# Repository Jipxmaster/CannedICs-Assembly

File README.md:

Son archivos viejos que tengo
-El compilador es un ejecutable que usa el archivo config
-EL archivo de la computadora está en formato .circ para logisim
-Correr la simulación a 4096 Hz, es muy lento

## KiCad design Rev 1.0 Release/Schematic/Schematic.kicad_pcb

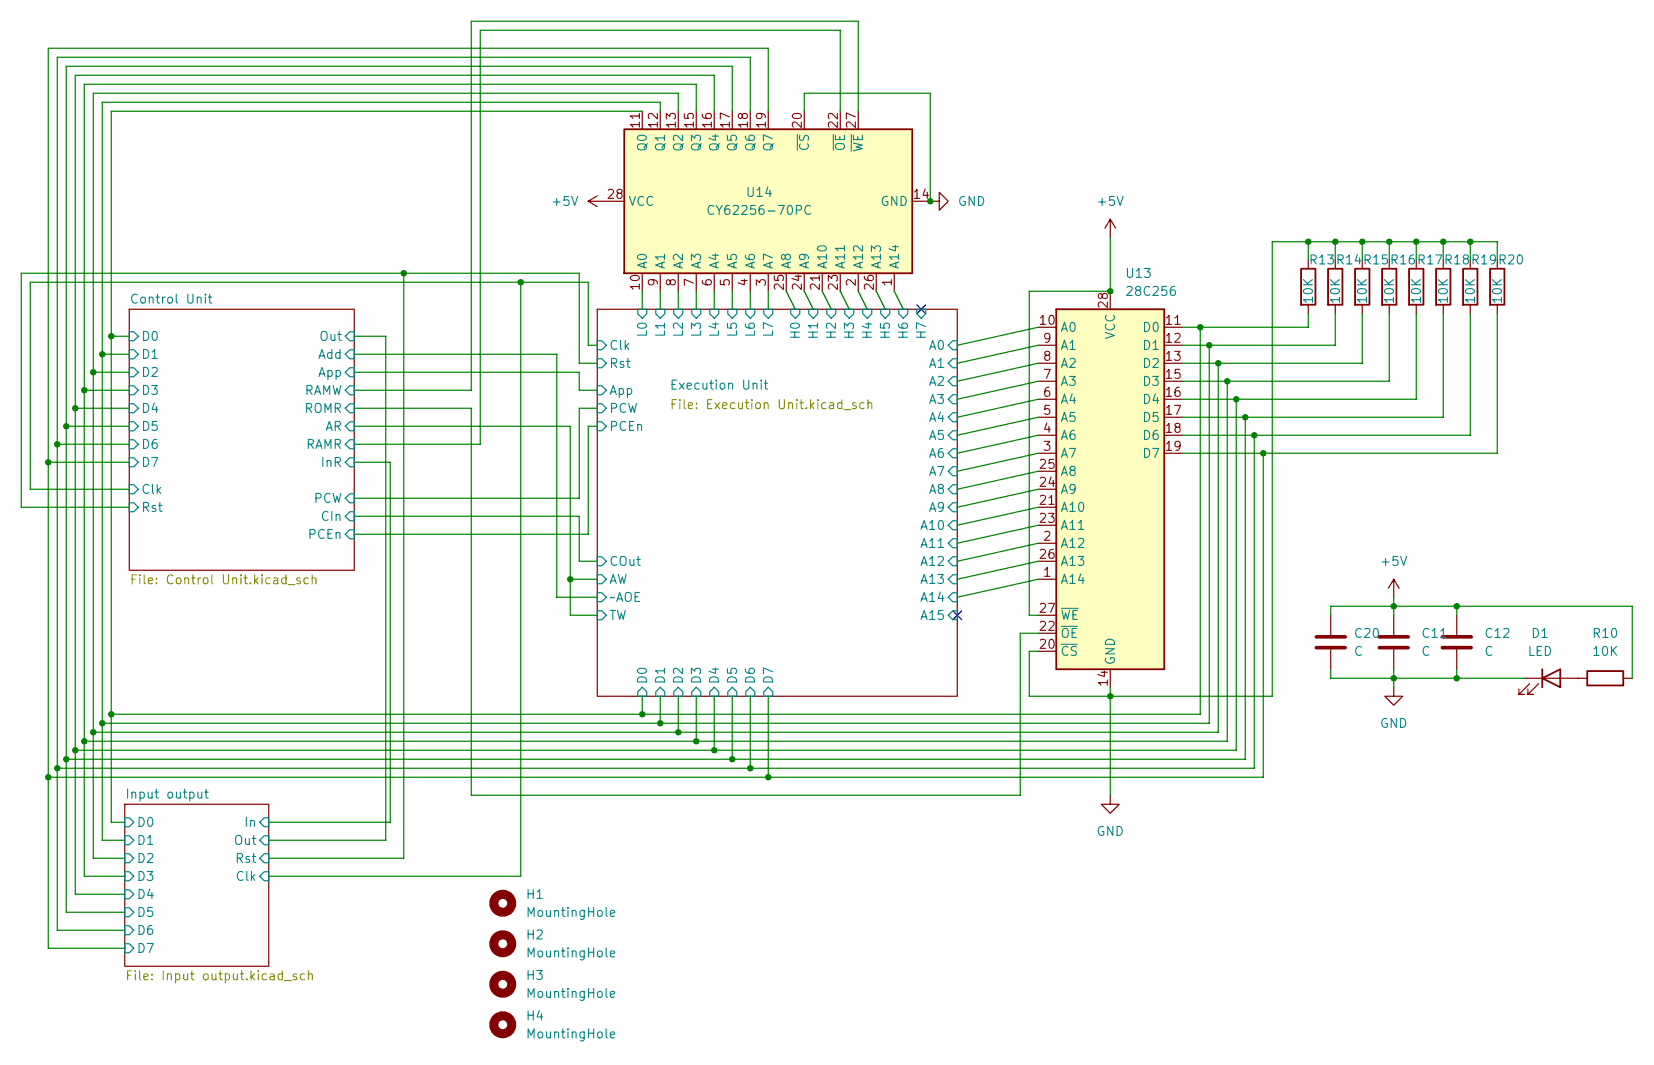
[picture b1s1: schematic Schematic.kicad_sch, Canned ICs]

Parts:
C11, C12: C; C_Disc_D3.8mm_W2.6mm_P2.50mm
C20: C; C_Radial_D5.0mm_H11.0mm_P2.00mm
D1: LED; LED_D3.0mm_Clear
H1, H2, H3, H4: MountingHole; MountingHole_3.2mm_M3_ISO7380
R10: 10K; R_Axial_DIN0204_L3.6mm_D1.6mm_P7.62mm_Horizontal
R13, R14, R15, R16, R17, R18, R19, R20: 10K; R_Axial_DIN0204_L3.6mm_D1.6mm_P2.54mm_Vertical
U13: 28C256; DIP-28_W15.24mm
U14: CY62256-70PC; DIP-28_W15.24mm

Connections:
+5V: C11.1, C12.1, C20.1, R10.2, U13.27 (~WE), U13.28 (VCC), U14.28 (VCC); also elsewhere on the board
/Control Unit/D0: R13.2, U13.11 (D0), U14.11 (Q0); also elsewhere on the board
/Control Unit/D1: R14.2, U13.12 (D1), U14.12 (Q1); also elsewhere on the board
/Control Unit/D2: R15.2, U13.13 (D2), U14.13 (Q2); also elsewhere on the board
/Control Unit/D3: R16.2, U13.15 (D3), U14.15 (Q3); also elsewhere on the board
/Control Unit/D4: R17.2, U13.16 (D4), U14.16 (Q4); also elsewhere on the board
/Control Unit/D5: R18.2, U13.17 (D5), U14.17 (Q5); also elsewhere on the board
/Control Unit/D6: R19.2, U13.18 (D6), U14.18 (Q6); also elsewhere on the board
/Control Unit/D7: R20.2, U13.19 (D7), U14.19 (Q7); also elsewhere on the board
/Control Unit/RAMR: U14.22 (~OE); also elsewhere on the board
/Control Unit/RAMW: U14.27 (~WE); also elsewhere on the board
/Control Unit/ROMR: U13.22 (~OE); also elsewhere on the board
/Execution Unit/A0: U13.10 (A0); also elsewhere on the board
/Execution Unit/A1: U13.9 (A1); also elsewhere on the board
/Execution Unit/A2: U13.8 (A2); also elsewhere on the board
/Execution Unit/A3: U13.7 (A3); also elsewhere on the board
/Execution Unit/A4: U13.6 (A4); also elsewhere on the board
/Execution Unit/A5: U13.5 (A5); also elsewhere on the board
/Execution Unit/A6: U13.4 (A6); also elsewhere on the board
/Execution Unit/A7: U13.3 (A7); also elsewhere on the board
/Execution Unit/A8: U13.25 (A8); also elsewhere on the board
/Execution Unit/A9: U13.24 (A9); also elsewhere on the board
/Execution Unit/A10: U13.21 (A10); also elsewhere on the board
/Execution Unit/A11: U13.23 (A11); also elsewhere on the board
/Execution Unit/A12: U13.2 (A12); also elsewhere on the board
/Execution Unit/A13: U13.26 (A13); also elsewhere on the board
/Execution Unit/A14: U13.1 (A14); also elsewhere on the board
/Execution Unit/H0: U14.25 (A8); also elsewhere on the board
/Execution Unit/H1: U14.24 (A9); also elsewhere on the board
/Execution Unit/H2: U14.21 (A10); also elsewhere on the board
/Execution Unit/H3: U14.23 (A11); also elsewhere on the board
/Execution Unit/H4: U14.2 (A12); also elsewhere on the board
/Execution Unit/H5: U14.26 (A13); also elsewhere on the board
/Execution Unit/H6: U14.1 (A14); also elsewhere on the board
/Execution Unit/L0: U14.10 (A0); also elsewhere on the board
/Execution Unit/L1: U14.9 (A1); also elsewhere on the board
/Execution Unit/L2: U14.8 (A2); also elsewhere on the board
/Execution Unit/L3: U14.7 (A3); also elsewhere on the board
/Execution Unit/L4: U14.6 (A4); also elsewhere on the board
/Execution Unit/L5: U14.5 (A5); also elsewhere on the board
/Execution Unit/L6: U14.4 (A6); also elsewhere on the board
/Execution Unit/L7: U14.3 (A7); also elsewhere on the board
GND: C11.2, C12.2, C20.2, D1.1 (K), R13.1, R14.1, R15.1, R16.1, R17.1, R18.1, R19.1, R20.1, U13.14 (GND), U13.20 (~CS), U14.14 (GND), U14.20 (~CS); also elsewhere on the board
unnamed: D1.2 (A), R10.1

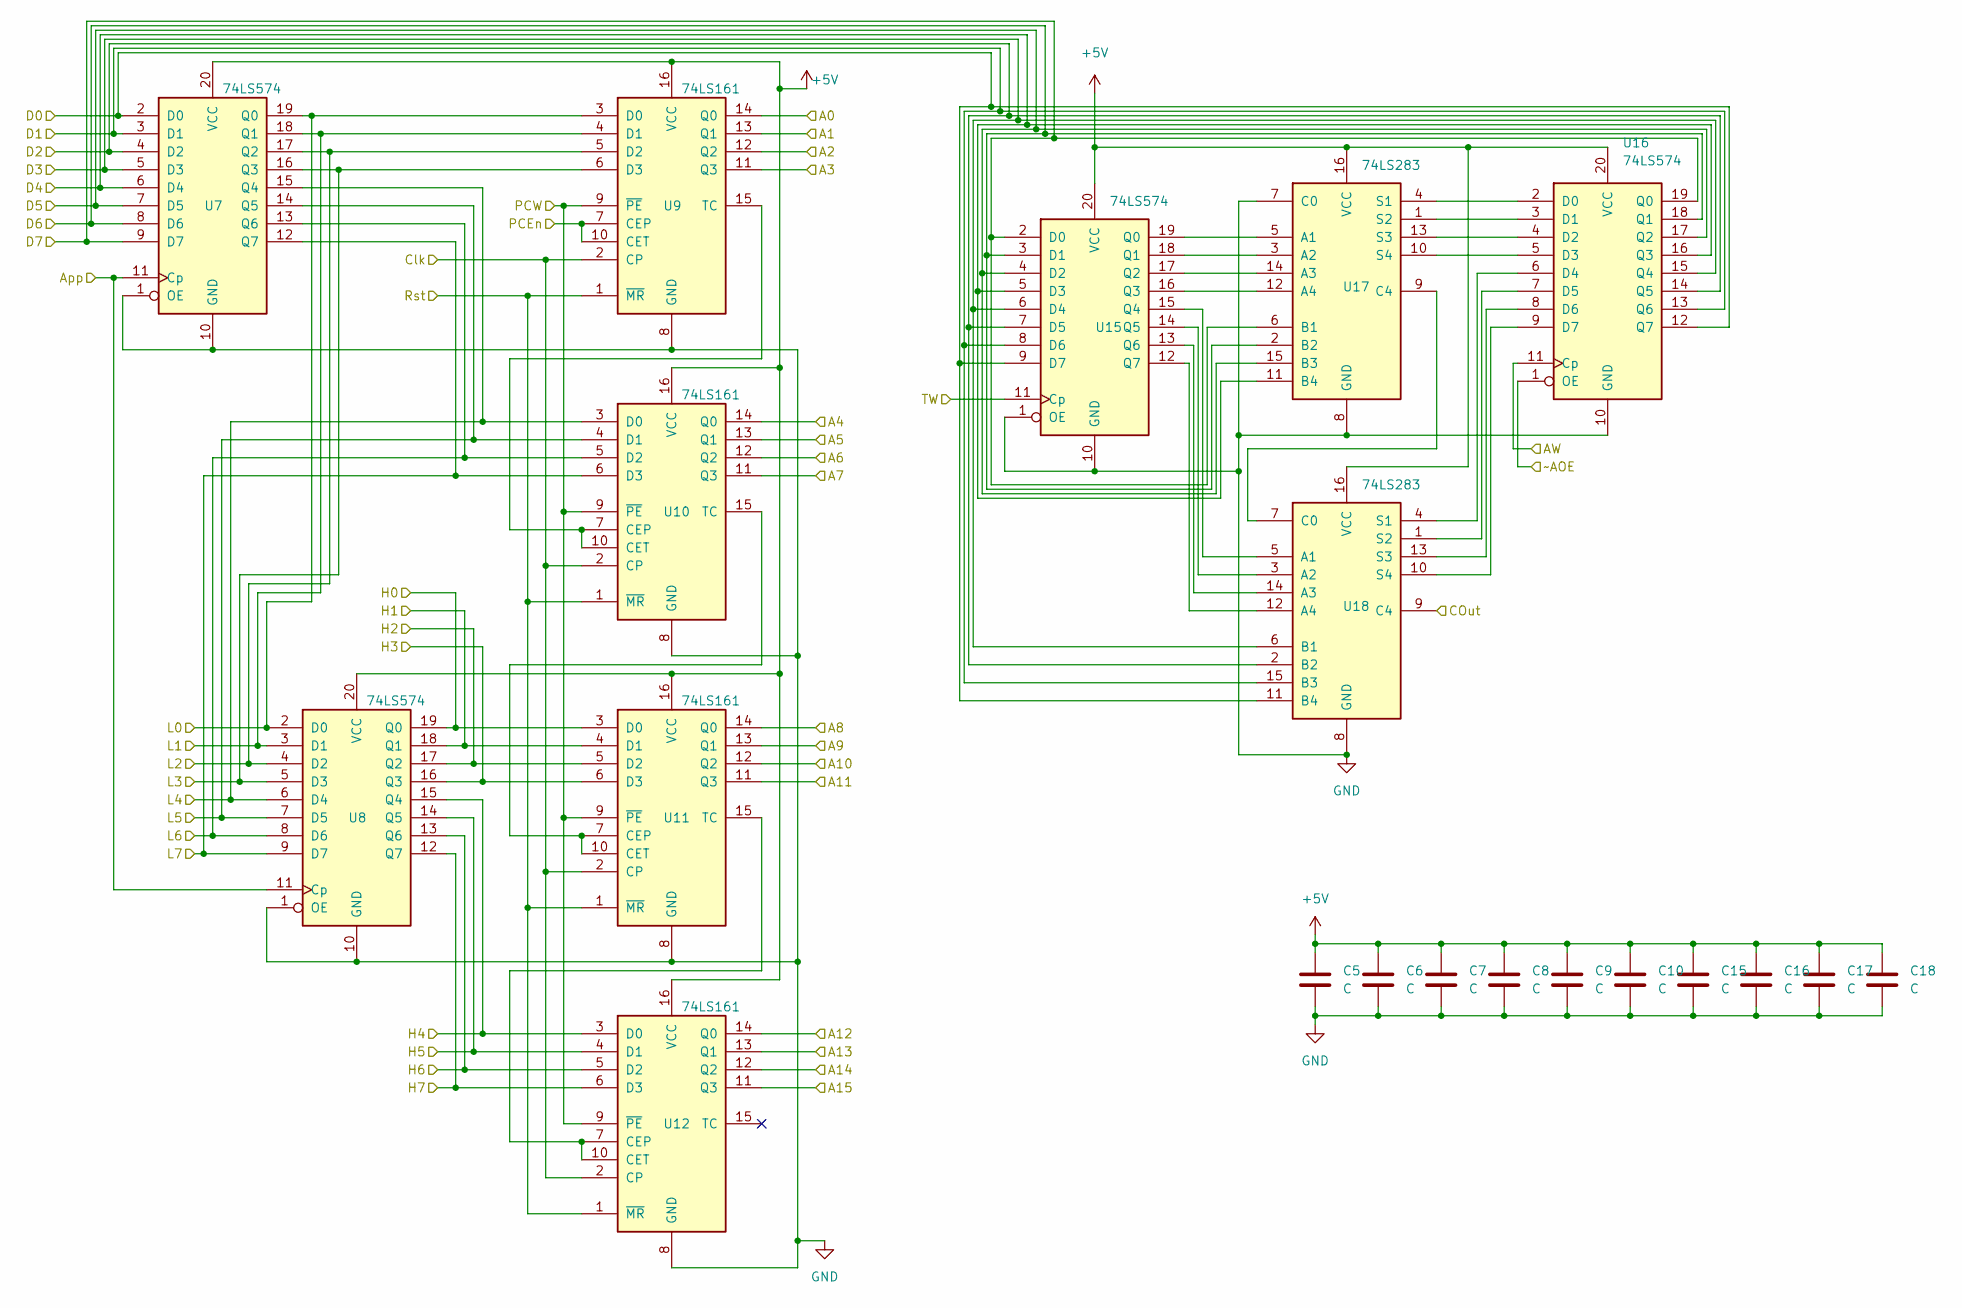
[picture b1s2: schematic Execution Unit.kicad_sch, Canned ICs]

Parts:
C5, C6, C7, C8, C9, C10, C15, C16, C17, C18: C; C_Disc_D3.8mm_W2.6mm_P2.50mm
U7, U8, U15, U16: 74LS574; DIP-20_W7.62mm
U9, U10, U11, U12: 74LS161; DIP-16_W7.62mm
U17, U18: 74LS283; DIP-16_W7.62mm

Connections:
+5V: C5.1, C6.1, C7.1, C8.1, C9.1, C10.1, C15.1, C16.1, C17.1, C18.1, U7.20 (VCC), U8.20 (VCC), U9.16 (VCC), U10.16 (VCC), U11.16 (VCC), U12.16 (VCC), U15.20 (VCC), U16.20 (VCC), U17.16 (VCC), U18.16 (VCC); also elsewhere on the board
/Control Unit/AR: U15.11 (Cp), U16.11 (Cp); also elsewhere on the board
/Control Unit/Add: U16.1 (OE); also elsewhere on the board
/Control Unit/App: U7.11 (Cp), U8.11 (Cp); also elsewhere on the board
/Control Unit/CIn: U18.9 (C4); also elsewhere on the board
/Control Unit/Clk: U9.2 (CP), U10.2 (CP), U11.2 (CP), U12.2 (CP); also elsewhere on the board
/Control Unit/D0: U7.2 (D0), U15.9 (D7), U16.12 (Q7), U18.11 (B4); also elsewhere on the board
/Control Unit/D1: U7.3 (D1), U15.8 (D6), U16.13 (Q6), U18.15 (B3); also elsewhere on the board
/Control Unit/D2: U7.4 (D2), U15.7 (D5), U16.14 (Q5), U18.2 (B2); also elsewhere on the board
/Control Unit/D3: U7.5 (D3), U15.6 (D4), U16.15 (Q4), U18.6 (B1); also elsewhere on the board
/Control Unit/D4: U7.6 (D4), U15.5 (D3), U16.16 (Q3), U17.11 (B4); also elsewhere on the board
/Control Unit/D5: U7.7 (D5), U15.4 (D2), U16.17 (Q2), U17.15 (B3); also elsewhere on the board
/Control Unit/D6: U7.8 (D6), U15.3 (D1), U16.18 (Q1), U17.2 (B2); also elsewhere on the board
/Control Unit/D7: U7.9 (D7), U15.2 (D0), U16.19 (Q0), U17.6 (B1); also elsewhere on the board
/Control Unit/PCEn: U9.7 (CEP), U9.10 (CET); also elsewhere on the board
/Control Unit/PCW: U9.9 (~PE), U10.9 (~PE), U11.9 (~PE), U12.9 (~PE); also elsewhere on the board
/Control Unit/Rst: U9.1 (~MR), U10.1 (~MR), U11.1 (~MR), U12.1 (~MR); also elsewhere on the board
/Execution Unit/A0: U9.14 (Q0); also elsewhere on the board
/Execution Unit/A1: U9.13 (Q1); also elsewhere on the board
/Execution Unit/A2: U9.12 (Q2); also elsewhere on the board
/Execution Unit/A3: U9.11 (Q3); also elsewhere on the board
/Execution Unit/A4: U10.14 (Q0); also elsewhere on the board
/Execution Unit/A5: U10.13 (Q1); also elsewhere on the board
/Execution Unit/A6: U10.12 (Q2); also elsewhere on the board
/Execution Unit/A7: U10.11 (Q3); also elsewhere on the board
/Execution Unit/A8: U11.14 (Q0); also elsewhere on the board
/Execution Unit/A9: U11.13 (Q1); also elsewhere on the board
/Execution Unit/A10: U11.12 (Q2); also elsewhere on the board
/Execution Unit/A11: U11.11 (Q3); also elsewhere on the board
/Execution Unit/A12: U12.14 (Q0); also elsewhere on the board
/Execution Unit/A13: U12.13 (Q1); also elsewhere on the board
/Execution Unit/A14: U12.12 (Q2); also elsewhere on the board
/Execution Unit/A15: U12.11 (Q3)
/Execution Unit/H0: U8.19 (Q0), U11.3 (D0); also elsewhere on the board
/Execution Unit/H1: U8.18 (Q1), U11.4 (D1); also elsewhere on the board
/Execution Unit/H2: U8.17 (Q2), U11.5 (D2); also elsewhere on the board
/Execution Unit/H3: U8.16 (Q3), U11.6 (D3); also elsewhere on the board
/Execution Unit/H4: U8.15 (Q4), U12.3 (D0); also elsewhere on the board
/Execution Unit/H5: U8.14 (Q5), U12.4 (D1); also elsewhere on the board
/Execution Unit/H6: U8.13 (Q6), U12.5 (D2); also elsewhere on the board
/Execution Unit/H7: U8.12 (Q7), U12.6 (D3)
/Execution Unit/L0: U7.19 (Q0), U8.2 (D0), U9.3 (D0); also elsewhere on the board
/Execution Unit/L1: U7.18 (Q1), U8.3 (D1), U9.4 (D1); also elsewhere on the board
/Execution Unit/L2: U7.17 (Q2), U8.4 (D2), U9.5 (D2); also elsewhere on the board
/Execution Unit/L3: U7.16 (Q3), U8.5 (D3), U9.6 (D3); also elsewhere on the board
/Execution Unit/L4: U7.15 (Q4), U8.6 (D4), U10.3 (D0); also elsewhere on the board
/Execution Unit/L5: U7.14 (Q5), U8.7 (D5), U10.4 (D1); also elsewhere on the board
/Execution Unit/L6: U7.13 (Q6), U8.8 (D6), U10.5 (D2); also elsewhere on the board
/Execution Unit/L7: U7.12 (Q7), U8.9 (D7), U10.6 (D3); also elsewhere on the board
GND: C5.2, C6.2, C7.2, C8.2, C9.2, C10.2, C15.2, C16.2, C17.2, C18.2, U7.1 (OE), U7.10 (GND), U8.1 (OE), U8.10 (GND), U9.8 (GND), U10.8 (GND), U11.8 (GND), U12.8 (GND), U15.1 (OE), U15.10 (GND), U16.10 (GND), U17.7 (C0), U17.8 (GND), U18.8 (GND); also elsewhere on the board
unnamed: U9.15 (TC), U10.7 (CEP), U10.10 (CET)
unnamed: U10.15 (TC), U11.7 (CEP), U11.10 (CET)
unnamed: U11.15 (TC), U12.7 (CEP), U12.10 (CET)
unnamed: U15.12 (Q7), U18.12 (A4)
unnamed: U15.13 (Q6), U18.14 (A3)
unnamed: U15.14 (Q5), U18.3 (A2)
unnamed: U15.15 (Q4), U18.5 (A1)
unnamed: U15.16 (Q3), U17.12 (A4)
unnamed: U15.17 (Q2), U17.14 (A3)
unnamed: U15.18 (Q1), U17.3 (A2)
unnamed: U15.19 (Q0), U17.5 (A1)
unnamed: U16.2 (D0), U17.4 (S1)
unnamed: U16.3 (D1), U17.1 (S2)
unnamed: U16.4 (D2), U17.13 (S3)
unnamed: U16.5 (D3), U17.10 (S4)
unnamed: U16.6 (D4), U18.4 (S1)
unnamed: U16.7 (D5), U18.1 (S2)
unnamed: U16.8 (D6), U18.13 (S3)
unnamed: U16.9 (D7), U18.10 (S4)
unnamed: U17.9 (C4), U18.7 (C0)

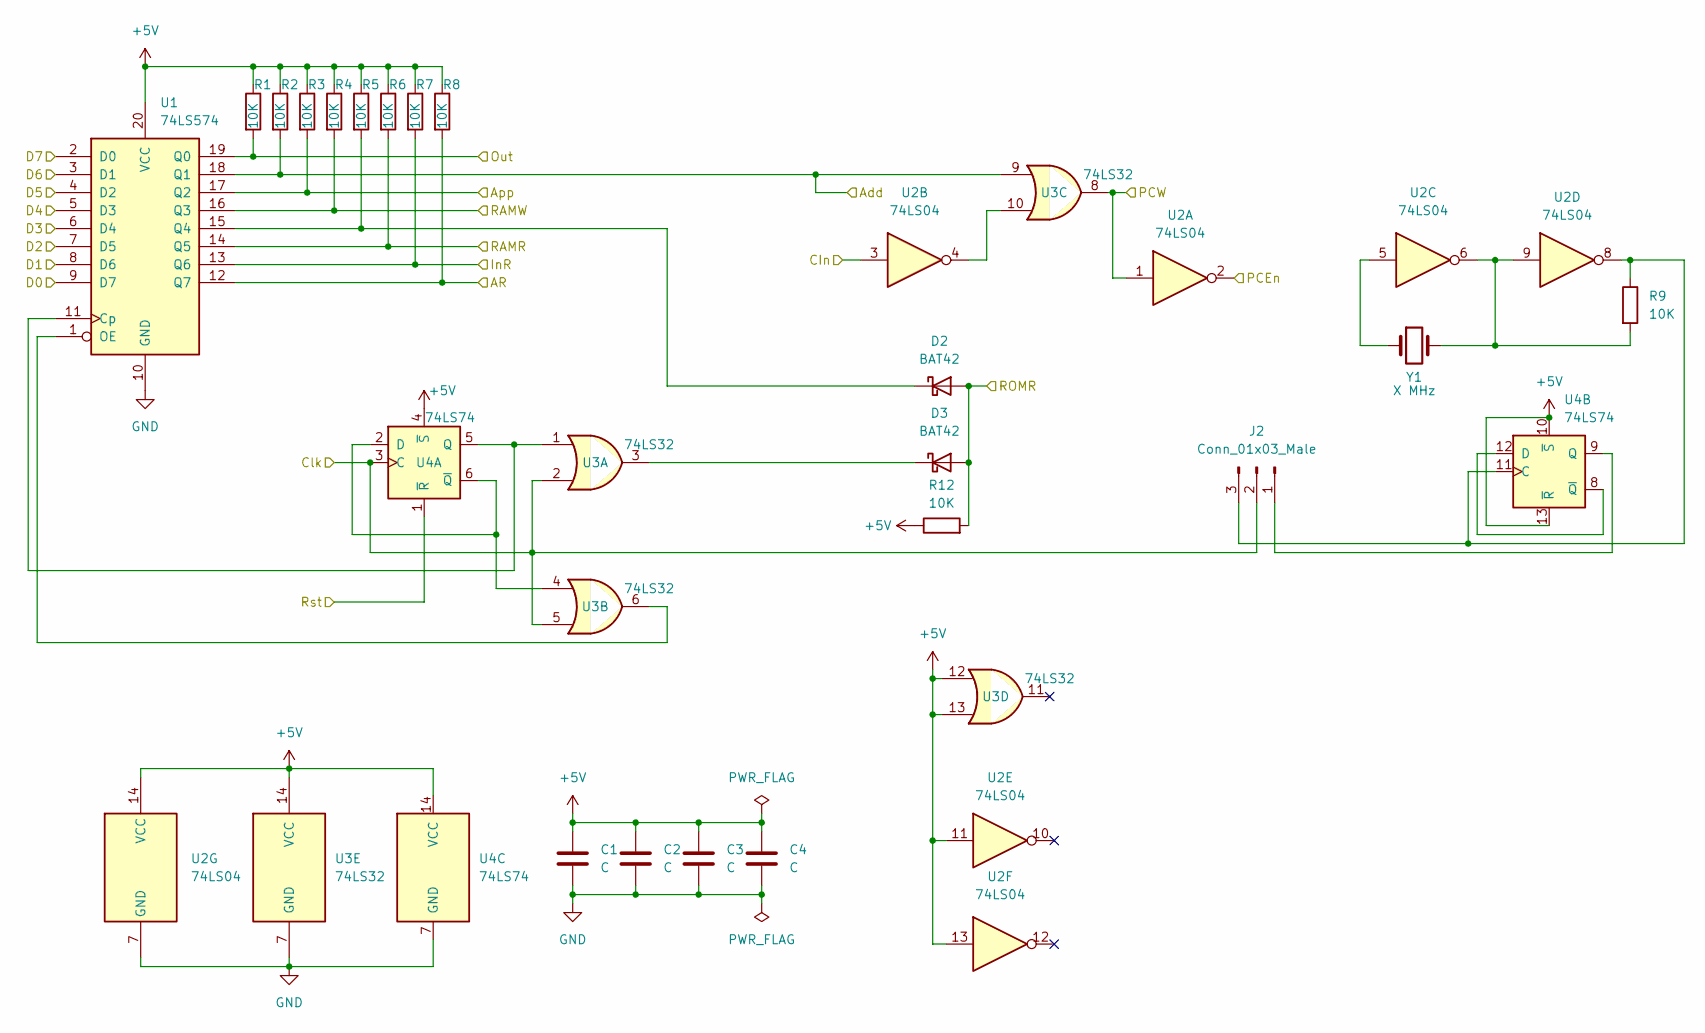
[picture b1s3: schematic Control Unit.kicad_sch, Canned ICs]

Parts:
C1, C2, C3, C4: C; C_Disc_D3.8mm_W2.6mm_P2.50mm
D2, D3: BAT42; D_DO-35_SOD27_P2.54mm_Vertical_AnodeUp
J2: Conn_01x03_Male; PinHeader_1x03_P2.54mm_Vertical
R1, R2, R3, R4, R5, R6, R7, R8, R9, R12: 10K; R_Axial_DIN0204_L3.6mm_D1.6mm_P2.54mm_Vertical
U1: 74LS574; DIP-20_W7.62mm
U2: 74LS04; DIP-14_W7.62mm
U3: 74LS32; DIP-14_W7.62mm
U4: 74LS74; DIP-14_W7.62mm
Y1: X MHz; Crystal_HC18-U_Vertical

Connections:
+5V: C1.1, C2.1, C3.1, C4.1, R1.1, R2.1, R3.1, R4.1, R5.1, R6.1, R7.1, R8.1, R12.1, U1.20 (VCC), U2.11, U2.13, U2.14 (VCC), U3.12, U3.13, U3.14 (VCC), U4.4 (~S), U4.10 (~S), U4.13 (~R), U4.14 (VCC); also elsewhere on the board
/Control Unit/AR: R8.2, U1.12 (Q7); also elsewhere on the board
/Control Unit/Add: R2.2, U1.18 (Q1), U3.9; also elsewhere on the board
/Control Unit/App: R3.2, U1.17 (Q2); also elsewhere on the board
/Control Unit/CIn: U2.3; also elsewhere on the board
/Control Unit/Clk: J2.2, U3.2, U3.5, U4.3 (C); also elsewhere on the board
/Control Unit/D0: U1.9 (D7); also elsewhere on the board
/Control Unit/D1: U1.8 (D6); also elsewhere on the board
/Control Unit/D2: U1.7 (D5); also elsewhere on the board
/Control Unit/D3: U1.6 (D4); also elsewhere on the board
/Control Unit/D4: U1.5 (D3); also elsewhere on the board
/Control Unit/D5: U1.4 (D2); also elsewhere on the board
/Control Unit/D6: U1.3 (D1); also elsewhere on the board
/Control Unit/D7: U1.2 (D0); also elsewhere on the board
/Control Unit/InR: R7.2, U1.13 (Q6); also elsewhere on the board
/Control Unit/Out: R1.2, U1.19 (Q0); also elsewhere on the board
/Control Unit/PCEn: U2.2; also elsewhere on the board
/Control Unit/PCW: U2.1, U3.8; also elsewhere on the board
/Control Unit/RAMR: R6.2, U1.14 (Q5); also elsewhere on the board
/Control Unit/RAMW: R4.2, U1.16 (Q3); also elsewhere on the board
/Control Unit/ROMR: D2.2 (A), D3.2 (A), R12.2; also elsewhere on the board
/Control Unit/Rst: U4.1 (~R); also elsewhere on the board
GND: C1.2, C2.2, C3.2, C4.2, U1.10 (GND), U2.7 (GND), U3.7 (GND), U4.7 (GND); also elsewhere on the board
unnamed: D2.1 (K), R5.2, U1.15 (Q4)
unnamed: D3.1 (K), U3.3
unnamed: J2.3, R9.1, U2.8, U4.11 (C)
unnamed: R9.2, U2.6, U2.9, Y1.2
unnamed: U1.1 (OE), U3.6
unnamed: U1.11 (Cp), U3.1, U4.5 (Q)
unnamed: U2.4, U3.10
unnamed: U2.5, Y1.1
unnamed: U3.4, U4.2 (D), U4.6 (~Q)
unnamed: J2.1, U4.9 (Q)
unnamed: U4.8 (~Q), U4.12 (D)

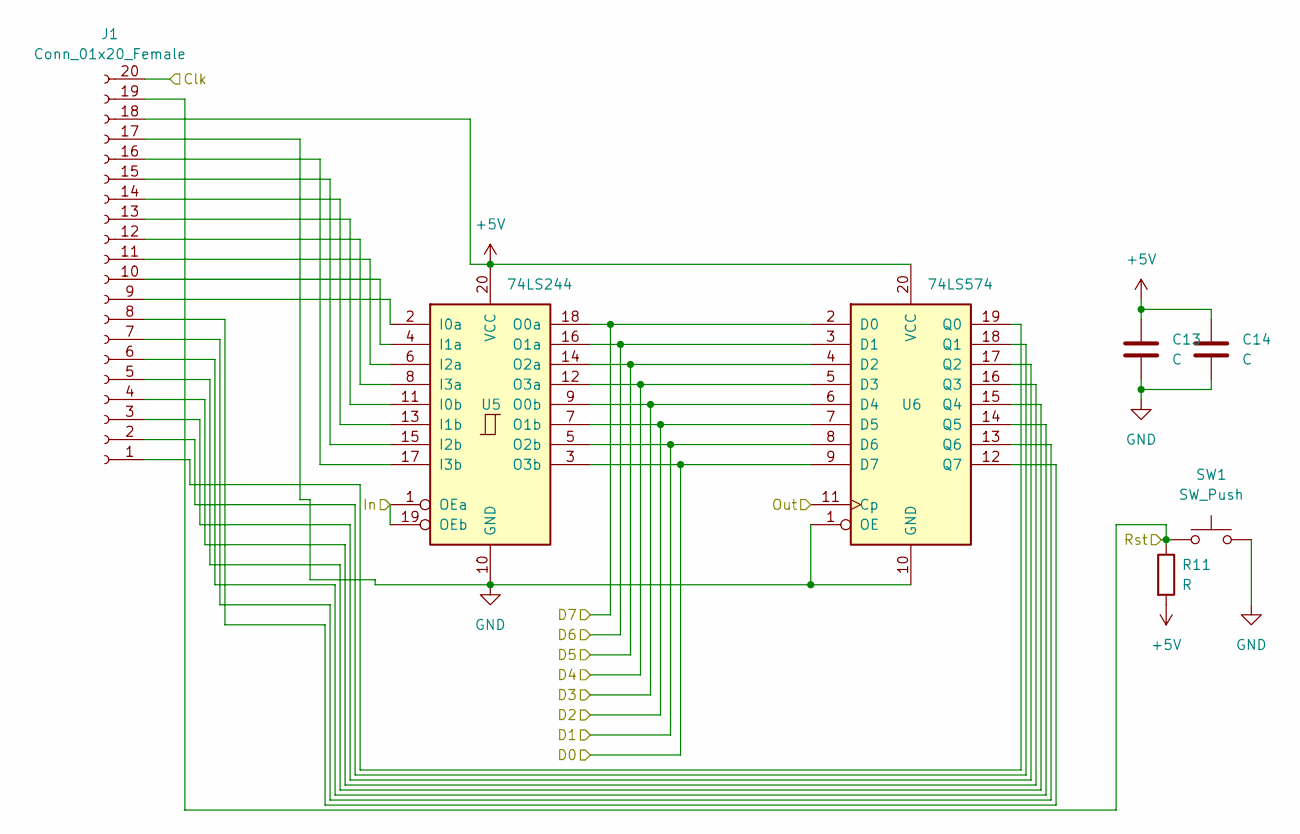
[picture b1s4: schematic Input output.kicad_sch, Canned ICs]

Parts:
C13, C14: C; C_Disc_D3.8mm_W2.6mm_P2.50mm
J1: Conn_01x20_Female; PinHeader_1x20_P2.54mm_Vertical
R11: R; R_Axial_DIN0204_L3.6mm_D1.6mm_P2.54mm_Vertical
SW1: SW_Push; SW_PUSH_6mm_H4.3mm
U5: 74LS244; DIP-20_W7.62mm
U6: 74LS574; DIP-20_W7.62mm

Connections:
+5V: C13.1, C14.1, J1.18, R11.2, U5.20 (VCC), U6.20 (VCC); also elsewhere on the board
/Control Unit/Clk: J1.20; also elsewhere on the board
/Control Unit/D0: U5.3 (O3b), U6.9 (D7); also elsewhere on the board
/Control Unit/D1: U5.5 (O2b), U6.8 (D6); also elsewhere on the board
/Control Unit/D2: U5.7 (O1b), U6.7 (D5); also elsewhere on the board
/Control Unit/D3: U5.9 (O0b), U6.6 (D4); also elsewhere on the board
/Control Unit/D4: U5.12 (O3a), U6.5 (D3); also elsewhere on the board
/Control Unit/D5: U5.14 (O2a), U6.4 (D2); also elsewhere on the board
/Control Unit/D6: U5.16 (O1a), U6.3 (D1); also elsewhere on the board
/Control Unit/D7: U5.18 (O0a), U6.2 (D0); also elsewhere on the board
/Control Unit/InR: U5.1 (OEa), U5.19 (OEb); also elsewhere on the board
/Control Unit/Out: U6.11 (Cp); also elsewhere on the board
/Control Unit/Rst: J1.19, R11.1, SW1.1; also elsewhere on the board
GND: C13.2, C14.2, J1.17, SW1.2, U5.10 (GND), U6.1 (OE), U6.10 (GND); also elsewhere on the board
unnamed: J1.1, U6.19 (Q0)
unnamed: J1.2, U6.18 (Q1)
unnamed: J1.3, U6.17 (Q2)
unnamed: J1.4, U6.16 (Q3)
unnamed: J1.5, U6.15 (Q4)
unnamed: J1.6, U6.14 (Q5)
unnamed: J1.7, U6.13 (Q6)
unnamed: J1.8, U6.12 (Q7)
unnamed: J1.9, U5.2 (I0a)
unnamed: J1.10, U5.4 (I1a)
unnamed: J1.11, U5.6 (I2a)
unnamed: J1.12, U5.8 (I3a)
unnamed: J1.13, U5.11 (I0b)
unnamed: J1.14, U5.13 (I1b)
unnamed: J1.15, U5.15 (I2b)
unnamed: J1.16, U5.17 (I3b)

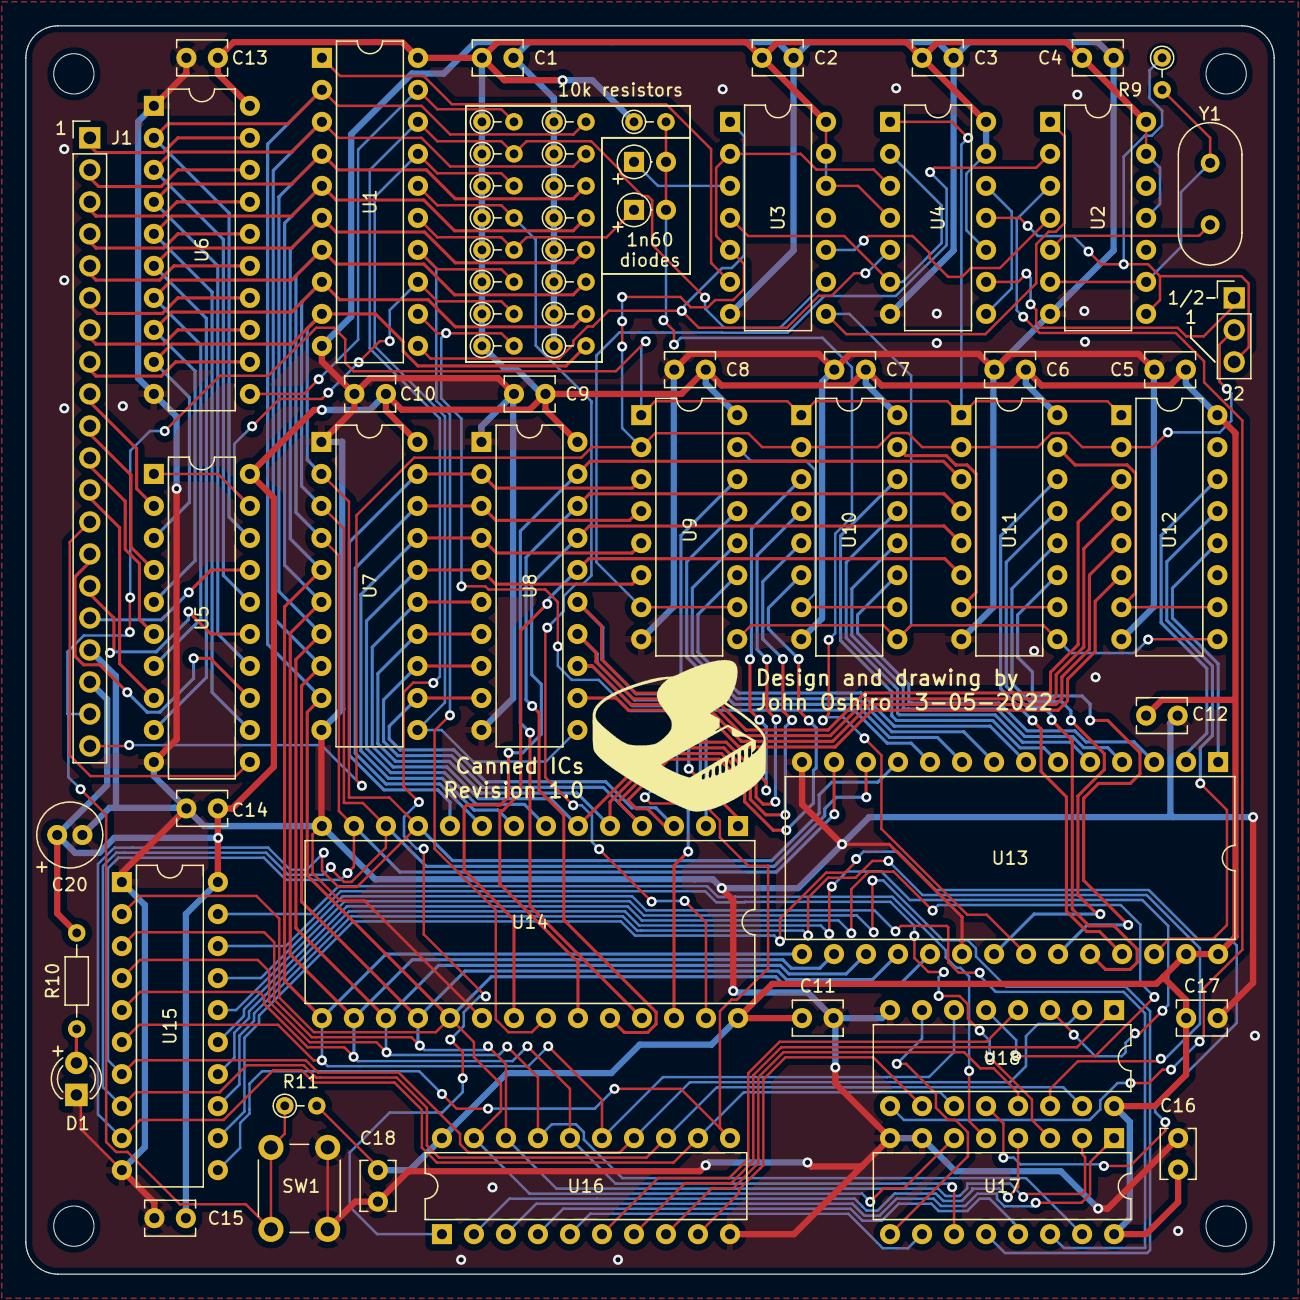
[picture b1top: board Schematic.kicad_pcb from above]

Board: 2 copper layers, 99.1 x 99.1 mm, 68 parts (0 on the bottom side), 102 nets.

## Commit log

2024-07-26 Parte 1
